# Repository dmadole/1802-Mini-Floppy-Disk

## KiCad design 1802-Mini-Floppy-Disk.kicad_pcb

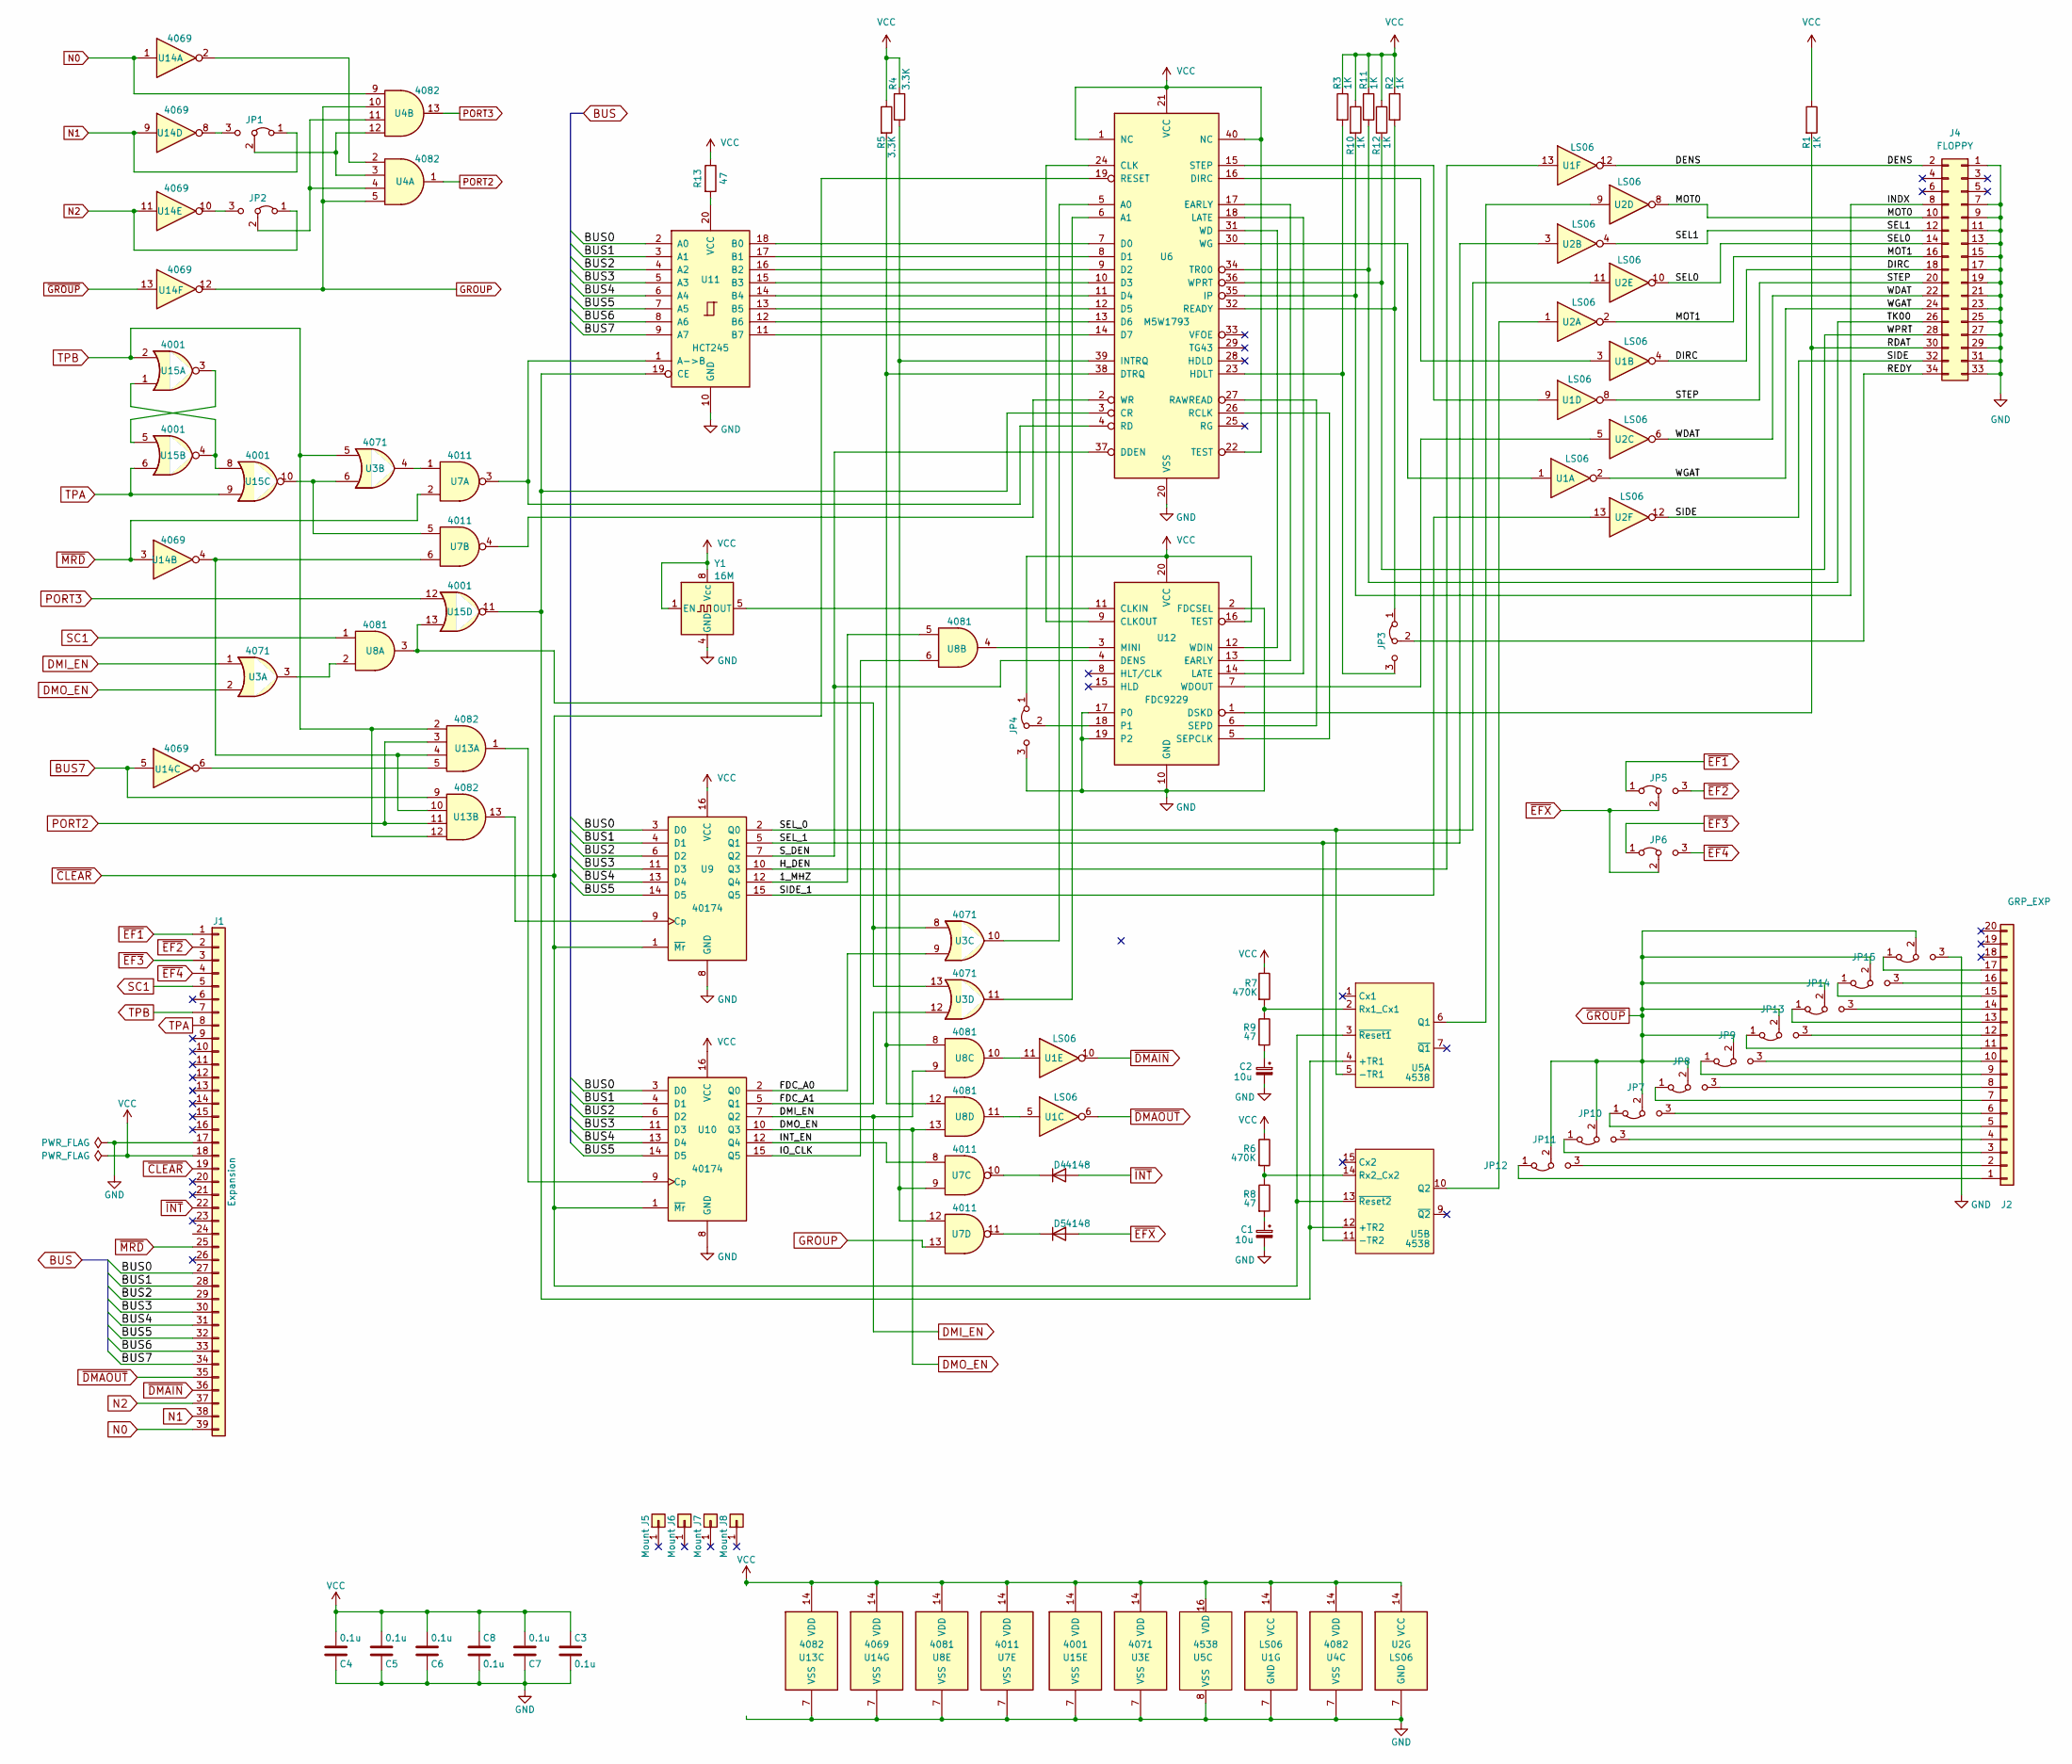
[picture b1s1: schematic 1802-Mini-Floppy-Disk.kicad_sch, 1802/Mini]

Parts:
C1, C2: 10u; CP_Radial_Tantal_D4.5mm_P2.50mm
C3, C4, C5, C6, C7, C8: 0.1u; C_Disc_D4.3mm_W1.9mm_P5.00mm
D4, D5: 4148; D_DO-35_SOD27_P7.62mm_Horizontal
J1: Expansion; PinSocket_1x39_P2.54mm_Vertical
J2: GRP_EXP; PinSocket_1x20_P2.54mm_Vertical
J4: FLOPPY; PinHeader_2x17_P2.54mm_Horizontal
J5, J6, J7, J8: Mount; 1pin
JP1, JP2, JP3, JP4: Jumper_3_Bridged12; PinHeader_1x03_P2.54mm_Vertical
JP5, JP7, JP8, JP9, JP10, JP11, JP12, JP13, JP14, JP15: EF1/2; PinHeader_1x03_P2.54mm_Vertical
JP6: EF3/4; PinHeader_1x03_P2.54mm_Vertical
R1, R2, R3, R10, R11, R12: 1K; R_Axial_DIN0207_L6.3mm_D2.5mm_P10.16mm_Horizontal
R4, R5: 3.3K; R_Axial_DIN0207_L6.3mm_D2.5mm_P10.16mm_Horizontal
R6, R7: 470K; R_Axial_DIN0207_L6.3mm_D2.5mm_P10.16mm_Horizontal
R8, R9, R13: 47; R_Axial_DIN0207_L6.3mm_D2.5mm_P10.16mm_Horizontal
U1, U2: LS06; DIP-14_W7.62mm_Socket
U3: 4071; DIP-14_W7.62mm_Socket
U4, U13: 4082; DIP-14_W7.62mm_Socket
U5: 4538; DIP-16_W7.62mm_Socket
U6: M5W1793; DIP-40_W15.24mm_Socket
U7: 4011; DIP-14_W7.62mm_Socket
U8: 4081; DIP-14_W7.62mm_Socket
U9, U10: 40174; DIP-16_W7.62mm_Socket
U11: HCT245; DIP-20_W7.62mm_Socket
U12: FDC9229; DIP-20_W7.62mm_Socket
U14: 4069; DIP-14_W7.62mm_Socket
U15: 4001; DIP-14_W7.62mm_Socket
Y1: 16M; Oscillator_DIP-8

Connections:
/1_MHZ: U8.5, U9.12 (Q4)
/BUS0: J1.27, U9.3 (D0), U10.3 (D0), U11.2 (A0)
/BUS1: J1.28, U9.4 (D1), U10.4 (D1), U11.3 (A1)
/BUS2: J1.29, U9.6 (D2), U10.6 (D2), U11.4 (A2)
/BUS3: J1.30, U9.11 (D3), U10.11 (D3), U11.5 (A3)
/BUS4: J1.31, U9.13 (D4), U10.13 (D4), U11.6 (A4)
/BUS5: J1.32, U9.14 (D5), U10.14 (D5), U11.7 (A5)
/BUS6: J1.33, U11.8 (A6)
/DENS: J4.2, U1.12
/DIRC: J4.18, U1.4
/FDC_A0: U3.9, U10.2 (Q0)
/FDC_A1: U3.12, U10.5 (Q1)
/H_DEN: U1.13, U9.10 (Q3)
/INDX: J4.8, R10.2, U6.35 (IP)
/INT_EN: U7.8, U10.12 (Q4)
/IO_CLK: U8.6, U10.15 (Q5)
/MOT0: J4.10, U2.8
/MOT1: J4.16, U2.2
/RDAT: J4.30, R1.2, U12.1 (DSKD)
/REDY: J4.34, JP3.2 (C)
/SEL0: J4.14, U2.10
/SEL1: J4.12, U2.4
/SEL_0: U2.11, U5.5 (-TR1), U9.2 (Q0)
/SEL_1: U2.3, U5.11 (-TR2), U9.5 (Q1)
/SIDE: J4.32, U2.12
/SIDE_1: U2.13, U9.15 (Q5)
/STEP: J4.20, U1.8
/S_DEN: U6.37 (DDEN), U9.7 (Q2), U12.4 (DENS)
/TK00: J4.26, R11.2, U6.34 (TR00)
/WDAT: J4.22, U2.6
/WGAT: J4.24, U1.2
/WPRT: J4.28, R12.2, U6.36 (WPRT)
BUS7: J1.34, U11.9 (A7), U13.9, U14.5
DMI_EN: U3.1, U8.9, U10.7 (Q2)
DMO_EN: U3.2, U8.13, U10.10 (Q3)
GND: C1.2, C2.2, C3.2, C4.1, C5.1, C6.1, C7.1, C8.2, J1.17, J4.1, J4.7, J4.9, J4.11, J4.13, J4.15, J4.17, J4.19, J4.21, J4.23, J4.25, J4.27, J4.29, J4.31, J4.33, JP4.3 (B), JP15.3 (B), U1.7 (GND), U2.7 (GND), U3.7 (VSS), U4.7 (VSS), U5.8 (VSS), U6.20 (VSS), U7.7 (VSS), U8.7 (VSS), U9.8 (GND), U10.8 (GND), U11.10 (GND), U12.2 (FDCSEL), U12.10 (GND), U12.17 (P0), U12.19 (P2), U13.7 (VSS), U14.7 (VSS), U15.7 (VSS), Y1.4 (GND)
GROUP: U4.5, U4.10, U7.13, U14.12
N0: J1.39, U4.9, U14.1
N1: J1.38, JP1.1 (A), U14.9
N2: J1.37, JP2.1 (A), U14.11
unnamed: C1.1, R8.2
unnamed: C2.1, R9.2
unnamed: D4.1 (K), U7.10
unnamed: D5.1 (K), U7.11
unnamed: J2.1, JP12.1 (A)
unnamed: J2.2, JP12.3 (B)
unnamed: J2.3, JP11.1 (A)
unnamed: J2.4, JP11.3 (B)
unnamed: J2.5, JP10.1 (A)
unnamed: J2.6, JP10.3 (B)
unnamed: J2.7, JP7.1 (A)
unnamed: J2.8, JP7.3 (B)
unnamed: J2.9, JP8.1 (A)
unnamed: J2.10, JP8.3 (B)
unnamed: J2.11, JP9.1 (A)
unnamed: J2.12, JP9.3 (B)
unnamed: J2.13, JP13.1 (A)
unnamed: J2.14, JP13.3 (B)
unnamed: J2.15, JP14.1 (A)
unnamed: J2.16, JP14.3 (B)
unnamed: J2.17, JP15.1 (A)
unnamed: JP1.3 (B), U14.8
unnamed: JP1.2 (C), U4.3, U4.12
unnamed: JP2.3 (B), U14.10
unnamed: JP2.2 (C), U4.4, U4.11
unnamed: JP3.1 (A), R2.2, U6.32 (READY)
unnamed: JP3.3 (B), R3.2, U6.23 (HDLT)
unnamed: JP4.2 (C), U12.18 (P1)
unnamed: U1.5, U8.11
unnamed: U1.11, U8.10
unnamed: U3.3, U8.2
unnamed: U3.4, U7.1
unnamed: U2.9, U5.6 (Q1)
unnamed: R7.2, R9.1, U5.2 (Rx1_Cx1)
unnamed: U2.1, U5.10 (Q2)
unnamed: R6.2, R8.1, U5.14 (Rx2_Cx2)
unnamed: U3.10, U6.5 (A0)
unnamed: U3.11, U6.6 (A1)
unnamed: U1.3, U6.16 (DIRC)
unnamed: R5.2, U6.38 (DTRQ), U8.8, U8.12
unnamed: R4.2, U6.39 (INTRQ), U7.9, U7.12
unnamed: U1.9, U6.15 (STEP)
unnamed: U1.1, U6.30 (WG)
unnamed: U6.2 (WR), U7.4
unnamed: U9.9 (Cp), U13.13
unnamed: U10.9 (Cp), U13.1
unnamed: U6.4 (RD), U7.3, U11.1 (A->B)
unnamed: U6.7 (D0), U11.18 (B0)
unnamed: U6.8 (D1), U11.17 (B1)
unnamed: U6.9 (D2), U11.16 (B2)
unnamed: U6.10 (D3), U11.15 (B3)
unnamed: U6.11 (D4), U11.14 (B4)
unnamed: U6.12 (D5), U11.13 (B5)
unnamed: U6.13 (D6), U11.12 (B6)
unnamed: U6.14 (D7), U11.11 (B7)
unnamed: U5.4 (+TR1), U5.12 (+TR2), U6.3 (CR), U11.19 (CE), U15.11
unnamed: R13.2, U11.20 (VCC)
unnamed: U12.11 (CLKIN), Y1.5 (OUT)
unnamed: U6.24 (CLK), U12.9 (CLKOUT)
unnamed: U6.17 (EARLY), U12.13 (EARLY)
unnamed: U6.18 (LATE), U12.14 (LATE)
unnamed: U8.4, U12.3 (MINI)
unnamed: U6.26 (RCLK), U12.5 (SEPCLK)
unnamed: U6.27 (RAWREAD), U12.6 (SEPD)
unnamed: U6.31 (WD), U12.12 (WDIN)
unnamed: U2.5, U12.7 (WDOUT)
unnamed: U13.5, U14.6
unnamed: U7.6, U13.4, U13.10, U14.4
unnamed: U4.2, U14.2
unnamed: U15.1, U15.4, U15.8
unnamed: U15.3, U15.5
unnamed: U3.6, U7.5, U15.10
unnamed: U3.8, U3.13, U8.3, U15.13
PORT2: U4.1, U13.3, U13.11
PORT3: U4.13, U15.12
SC1: J1.5, U8.1
TPA: J1.8, U15.6, U15.9
TPB: J1.7, U3.5, U13.2, U13.12, U15.2
VCC: C3.1, C4.2, C5.2, C6.2, C7.2, C8.1, J1.18, JP4.1 (A), R1.1, R2.1, R3.1, R4.1, R5.1, R6.1, R7.1, R10.1, R11.1, R12.1, R13.1, U1.14 (VCC), U2.14 (VCC), U3.14 (VDD), U4.14 (VDD), U5.16 (VDD), U6.1 (NC), U6.21 (VCC), U6.22 (TEST), U6.40 (NC), U7.14 (VDD), U8.14 (VDD), U9.16 (VCC), U10.16 (VCC), U12.16 (TEST), U12.20 (VCC), U13.14 (VDD), U14.14 (VDD), U15.14 (VDD), Y1.1 (EN), Y1.8 (Vcc)
~CLEAR: J1.19, U5.3 (~Reset1), U5.13 (~Reset2), U6.19 (RESET), U9.1 (~Mr), U10.1 (~Mr)
~DMAIN: J1.36, U1.10
~DMAOUT: J1.35, U1.6
~EF1: J1.1, JP5.1 (A)
~EF2: J1.2, JP5.3 (B)
~EF3: J1.3, JP6.1 (A)
~EF4: J1.4, JP6.3 (B)
~EFX: D5.2 (A), JP5.2 (C), JP6.2 (C)
~GROUP: JP7.2 (C), JP8.2 (C), JP9.2 (C), JP10.2 (C), JP11.2 (C), JP12.2 (C), JP13.2 (C), JP14.2 (C), JP15.2 (C), U14.13
~INT: D4.2 (A), J1.22
~MRD: J1.25, U7.2, U14.3

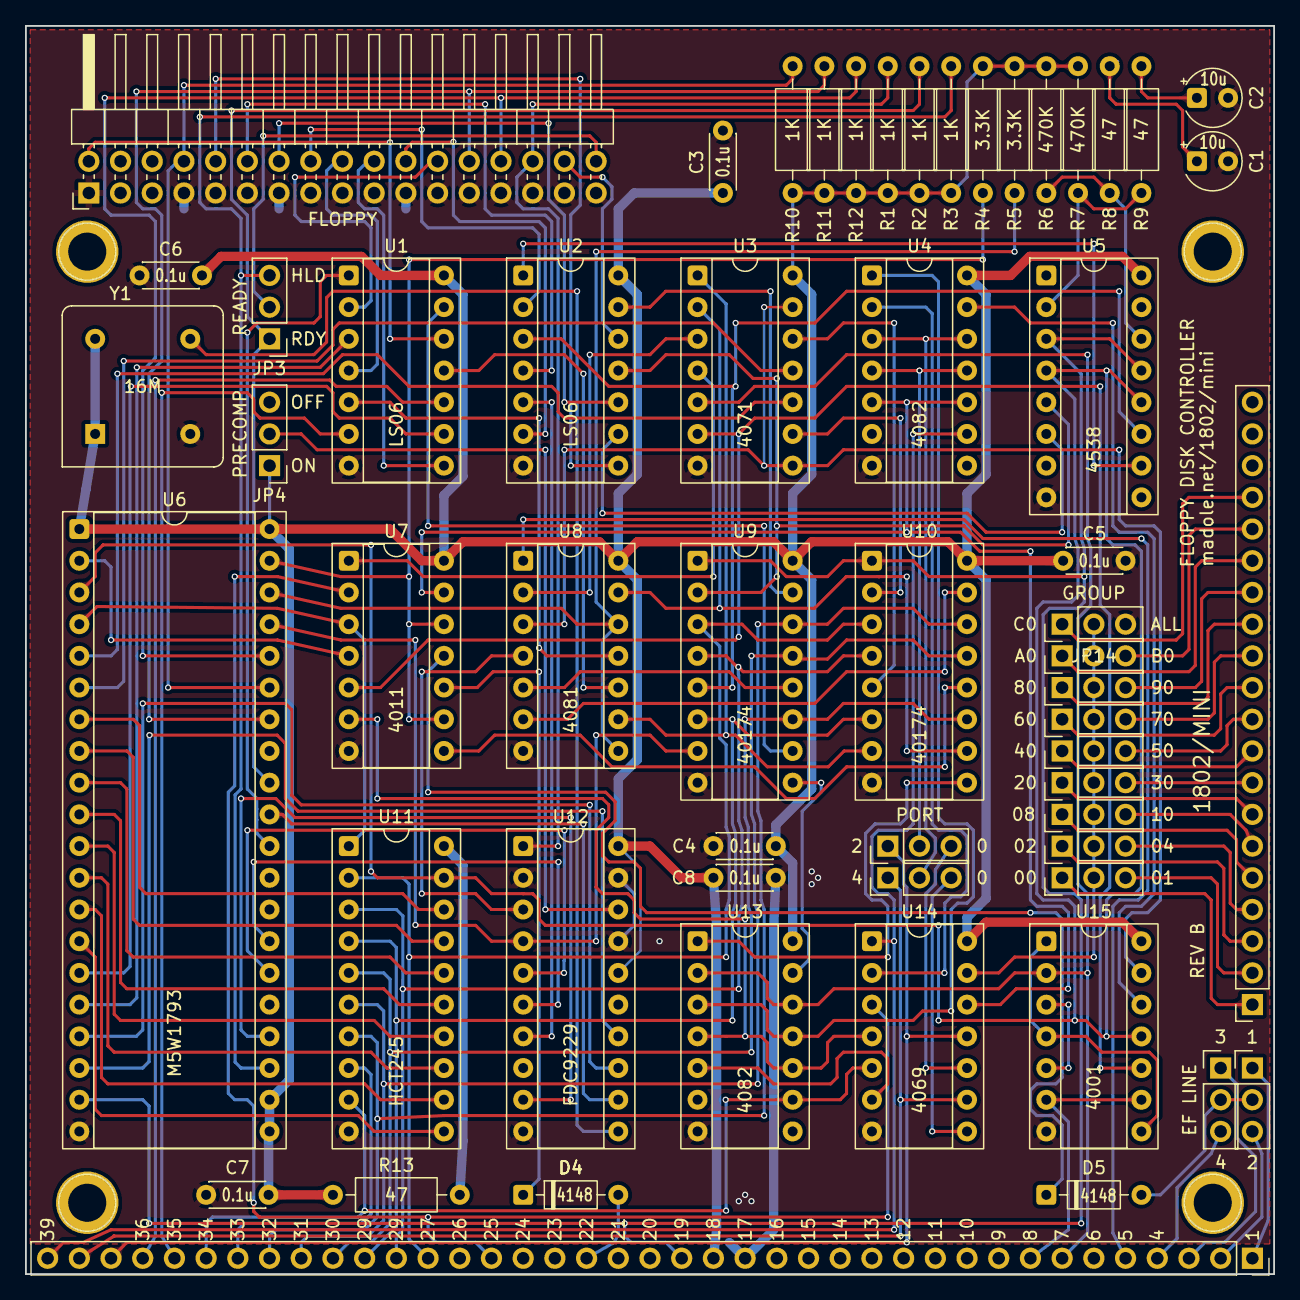
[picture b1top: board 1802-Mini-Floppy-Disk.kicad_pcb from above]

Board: 2 copper layers, 100.0 x 100.0 mm, 61 parts (0 on the bottom side), 130 nets.

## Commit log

2026-06-22 Delete 1802-Mini-Floppy-Disk-New.kicad_pcb
    File added in error
